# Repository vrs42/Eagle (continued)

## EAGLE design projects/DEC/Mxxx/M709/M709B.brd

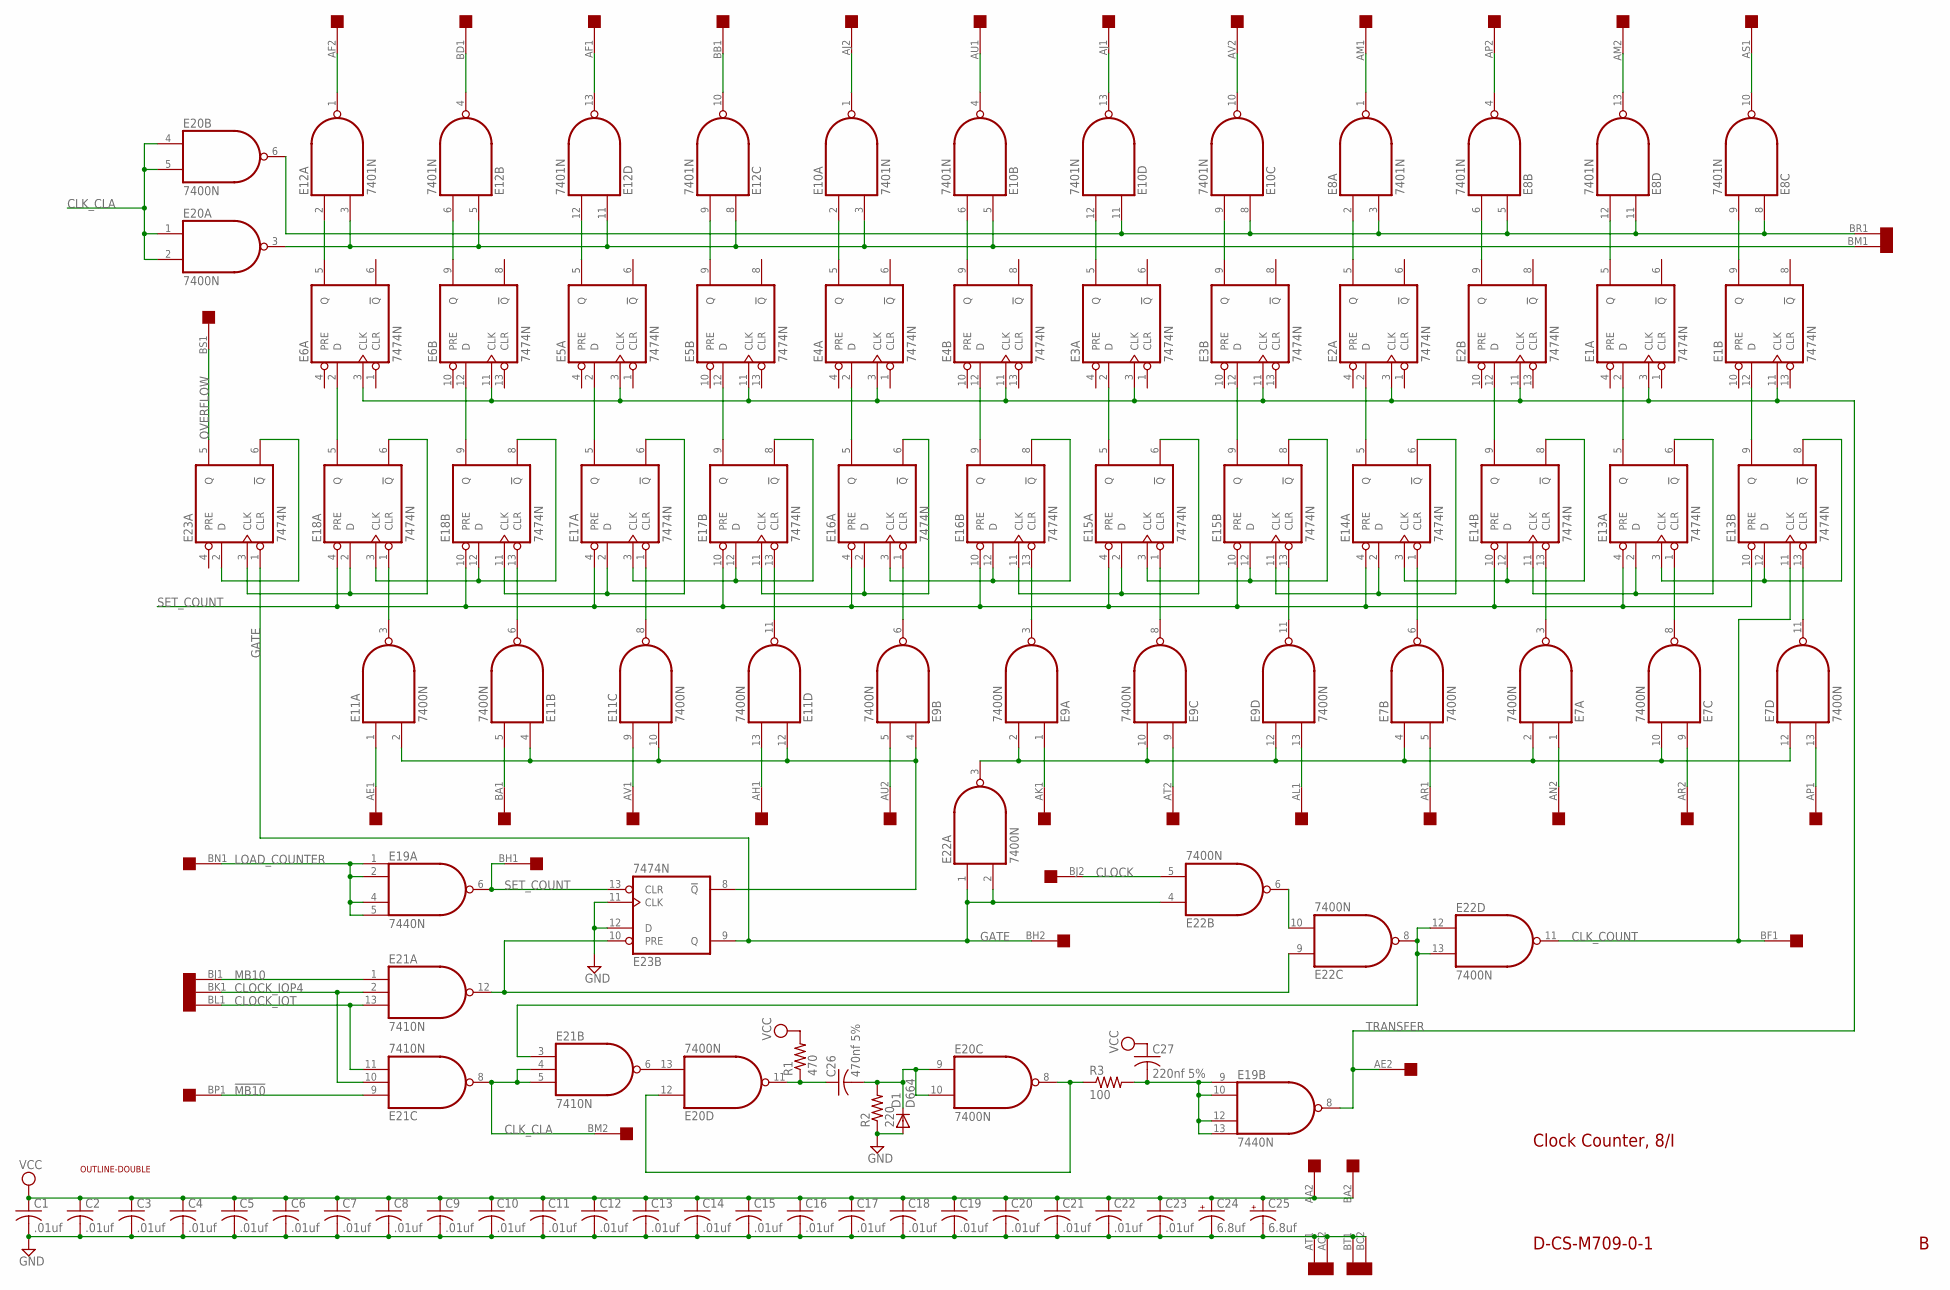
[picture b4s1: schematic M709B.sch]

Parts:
C1, C2, C3, C4, C5, C6, C7, C8, C9, C10, C11, C12, C13, C14, C15, C16, C17, C18, C19, C20, C21, C22, C23: .01uf; C050-025X075
C24, C25: 6.8uf; E15-5
C26: 470nf 5%; C050-025X075
C27: 220nf 5%; C050-025X075
D1: D664; DO35-10
E1, E2, E3, E4, E5, E6, E13, E14, E15, E16, E17, E18, E23: 7474N; DIL14
E7, E9, E11, E20, E22: 7400N; DIL14
E8, E10, E12: 7401N; DIL14
E19: 7440N; DIL14
E21: 7410N; DIL14
R1: 470; 0207/10
R2: 220; 0207/10
R3: 100; 0207/10
U$1: OUTLINE-DOUBLE; DOUBLE
U$2: DOUBLE; EDGE-CON4

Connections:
!MB10: E21.9 (I0), U$2.BP1
CLK_CLA: E20.1 (I0), E20.2 (I1), E20.4 (I0), E20.5 (I1), E21.4 (I1), E21.5 (I2), E21.8 (O), U$2.BM2
CLK_COUNT: E13.11 (CLK), E22.11 (O), U$2.BF1
CLOCK: E22.5 (I1), U$2.BJ2
CLOCK_IOP4: E21.2 (I1), E21.10 (I1), U$2.BK1
CLOCK_IOT: E21.11 (I2), E21.13 (I2), U$2.BL1
GATE: E22.1 (I0), E22.2 (I1), E22.4 (I0), E23.1 (CLR), E23.9 (Q), U$2.BH2
GND: C1.2, C2.2, C3.2, C4.2, C5.2, C6.2, C7.2, C8.2, C9.2, C10.2, C11.2, C12.2, C13.2, C14.2, C15.2, C16.2, C17.2, C18.2, C19.2, C20.2, C21.2, C22.2, C23.2, C24.-, C25.-, D1.A, E1.7 (GND), E2.7 (GND), E3.7 (GND), E4.7 (GND), E5.7 (GND), E6.7 (GND), E7.7 (GND), E8.7 (GND), E9.7 (GND), E10.7 (GND), E11.7 (GND), E12.7 (GND), E13.7 (GND), E14.7 (GND), E15.7 (GND), E16.7 (GND), E17.7 (GND), E18.7 (GND), E19.7 (GND), E20.7 (GND), E21.7 (GND), E22.7 (GND), E23.7 (GND), E23.11 (CLK), E23.12 (D), R2.1, U$2.AC2, U$2.AT1, U$2.BC2, U$2.BT1
LOAD_COUNTER: E19.1 (I0), E19.2 (I1), E19.4 (I2), E19.5 (I3), U$2.BN1
MB10: E21.1 (I0), U$2.BJ1
unnamed: E1.9 (Q), E8.9 (I1)
unnamed: E1.5 (Q), E8.12 (I1)
unnamed: E2.9 (Q), E8.6 (I1)
unnamed: E2.5 (Q), E8.2 (I0)
unnamed: E6.5 (Q), E12.2 (I0)
unnamed: E3.9 (Q), E10.9 (I1)
unnamed: E3.5 (Q), E10.12 (I1)
unnamed: E4.5 (Q), E10.2 (I0)
unnamed: E4.9 (Q), E10.6 (I1)
unnamed: E5.5 (Q), E12.12 (I1)
unnamed: E5.9 (Q), E12.9 (I1)
unnamed: E6.9 (Q), E12.6 (I1)
unnamed: E10.3 (I1), E10.5 (I0), E12.3 (I1), E12.5 (I0), E12.8 (I0), E12.11 (I0), E20.3 (O), U$2.BM1
unnamed: E8.1 (O), U$2.AM1
unnamed: E8.4 (O), U$2.AP2
unnamed: E8.13 (O), U$2.AM2
unnamed: E8.10 (O), U$2.AS1
unnamed: E10.13 (O), U$2.AJ1
unnamed: E10.4 (O), U$2.AU1
unnamed: E10.1 (O), U$2.AJ2
unnamed: E10.10 (O), U$2.AV2
unnamed: E12.1 (O), U$2.AF2
unnamed: E12.4 (O), U$2.BD1
unnamed: E12.13 (O), U$2.AF1
unnamed: E12.10 (O), U$2.BB1
unnamed: E8.3 (I1), E8.5 (I0), E8.8 (I0), E8.11 (I0), E10.8 (I0), E10.11 (I0), E20.6 (O), U$2.BR1
unnamed: E6.2 (D), E18.5 (Q)
unnamed: E6.12 (D), E18.9 (Q)
unnamed: E5.2 (D), E17.5 (Q)
unnamed: E5.12 (D), E17.9 (Q)
unnamed: E4.2 (D), E16.5 (Q)
unnamed: E4.12 (D), E16.9 (Q)
unnamed: E3.2 (D), E15.5 (Q)
unnamed: E3.12 (D), E15.9 (Q)
unnamed: E2.2 (D), E14.5 (Q)
unnamed: E2.12 (D), E14.9 (Q)
unnamed: E1.2 (D), E13.5 (Q)
unnamed: E1.12 (D), E13.9 (Q)
unnamed: E13.3 (CLK), E13.8 (!Q), E13.12 (D)
unnamed: E13.2 (D), E13.6 (!Q), E14.11 (CLK)
unnamed: E14.3 (CLK), E14.8 (!Q), E14.12 (D)
unnamed: E14.2 (D), E14.6 (!Q), E15.11 (CLK)
unnamed: E15.3 (CLK), E15.8 (!Q), E15.12 (D)
unnamed: E15.2 (D), E15.6 (!Q), E16.11 (CLK)
unnamed: E16.3 (CLK), E16.8 (!Q), E16.12 (D)
unnamed: E16.2 (D), E16.6 (!Q), E17.11 (CLK)
unnamed: E17.3 (CLK), E17.8 (!Q), E17.12 (D)
unnamed: E17.2 (D), E17.6 (!Q), E18.11 (CLK)
unnamed: E18.3 (CLK), E18.8 (!Q), E18.12 (D)
unnamed: E18.2 (D), E18.6 (!Q), E23.3 (CLK)
unnamed: E23.2 (D), E23.6 (!Q)
unnamed: E7.6 (O), E14.1 (CLR)
unnamed: E7.3 (O), E14.13 (CLR)
unnamed: E7.8 (O), E13.1 (CLR)
unnamed: E7.11 (O), E13.13 (CLR)
unnamed: E7.2 (I1), E7.4 (I0), E7.10 (I1), E7.12 (I0), E9.2 (I1), E9.10 (I1), E9.12 (I0), E22.3 (O)
unnamed: E9.4 (I0), E11.2 (I1), E11.4 (I0), E11.10 (I1), E11.12 (I0), E23.8 (!Q)
unnamed: E22.6 (O), E22.10 (I1)
unnamed: E7.13 (I1), U$2.AP1
unnamed: E9.6 (O), E16.1 (CLR)
unnamed: E9.3 (O), E16.13 (CLR)
unnamed: E9.8 (O), E15.1 (CLR)
unnamed: E9.11 (O), E15.13 (CLR)
unnamed: E11.11 (O), E17.13 (CLR)
unnamed: E11.8 (O), E17.1 (CLR)
unnamed: E11.6 (O), E18.13 (CLR)
unnamed: E11.3 (O), E18.1 (CLR)
unnamed: E7.9 (I0), U$2.AR2
unnamed: E7.1 (I0), U$2.AN2
unnamed: E7.5 (I1), U$2.AR1
unnamed: E9.13 (I1), U$2.AL1
unnamed: E9.1 (I0), U$2.AK1
unnamed: E9.9 (I0), U$2.AT2
unnamed: E11.9 (I0), U$2.AV1
unnamed: E11.13 (I1), U$2.AH1
unnamed: E9.5 (I1), U$2.AU2
unnamed: E11.1 (I0), U$2.AE1
unnamed: E11.5 (I1), U$2.BA1
unnamed: E21.12 (O), E22.9 (I0), E23.10 (PRE)
unnamed: E21.3 (I0), E22.8 (O), E22.12 (I0), E22.13 (I1)
unnamed: C26.2, D1.C, E20.9 (I0), E20.10 (I1), R2.2
unnamed: E20.13 (I1), E21.6 (O)
unnamed: C27.2, E19.9 (I0), E19.10 (I1), E19.12 (I2), E19.13 (I3), R3.2
unnamed: C26.1, E20.11 (O), R1.1
unnamed: E20.8 (O), E20.12 (I0), R3.1
OVERFLOW: E23.5 (Q), U$2.BS1
SET_COUNT: E13.4 (PRE), E13.10 (PRE), E14.4 (PRE), E14.10 (PRE), E15.4 (PRE), E15.10 (PRE), E16.4 (PRE), E16.10 (PRE), E17.4 (PRE), E17.10 (PRE), E18.4 (PRE), E18.10 (PRE), E19.6 (O), E23.13 (CLR), U$2.BH1
TRANSFER: E1.3 (CLK), E1.11 (CLK), E2.3 (CLK), E2.11 (CLK), E3.3 (CLK), E3.11 (CLK), E4.3 (CLK), E4.11 (CLK), E5.3 (CLK), E5.11 (CLK), E6.3 (CLK), E6.11 (CLK), E19.8 (O), U$2.AE2
VCC: C1.1, C2.1, C3.1, C4.1, C5.1, C6.1, C7.1, C8.1, C9.1, C10.1, C11.1, C12.1, C13.1, C14.1, C15.1, C16.1, C17.1, C18.1, C19.1, C20.1, C21.1, C22.1, C23.1, C24.+, C25.+, C27.1, E1.14 (VCC), E2.14 (VCC), E3.14 (VCC), E4.14 (VCC), E5.14 (VCC), E6.14 (VCC), E7.14 (VCC), E8.14 (VCC), E9.14 (VCC), E10.14 (VCC), E11.14 (VCC), E12.14 (VCC), E13.14 (VCC), E14.14 (VCC), E15.14 (VCC), E16.14 (VCC), E17.14 (VCC), E18.14 (VCC), E19.14 (VCC), E20.14 (VCC), E21.14 (VCC), E22.14 (VCC), E23.14 (VCC), R1.2, U$2.AA2, U$2.BA2

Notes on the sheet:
Clock Counter, 8/I
D-CS-M709-0-1

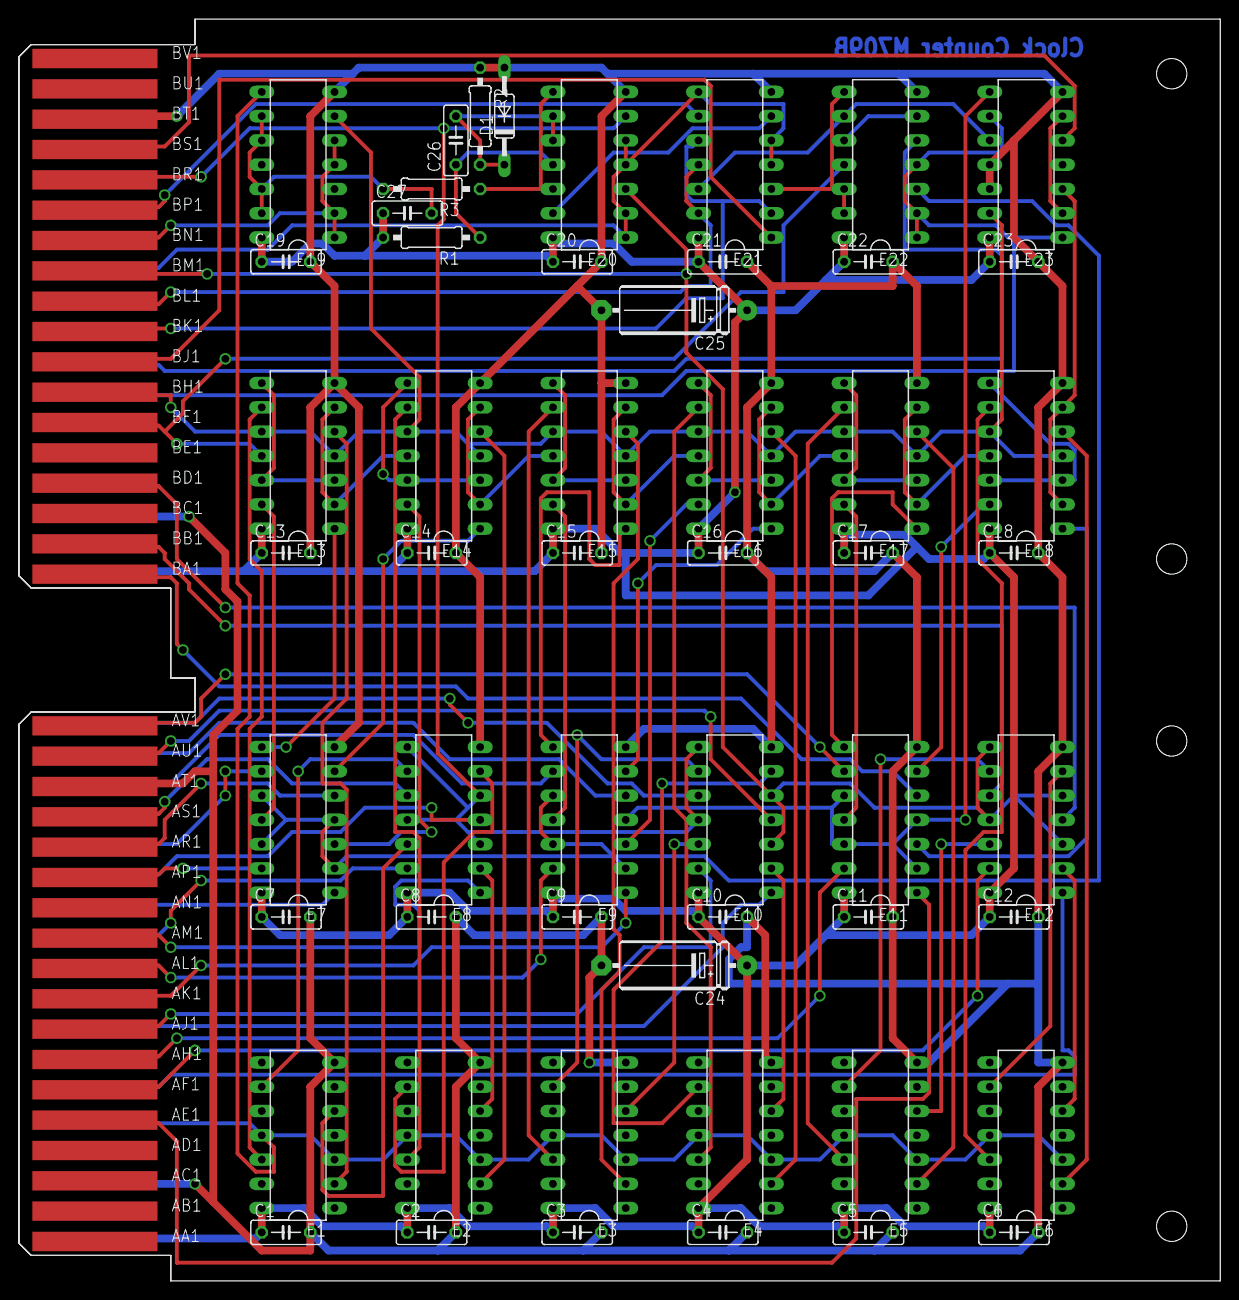
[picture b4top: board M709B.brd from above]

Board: 2 copper layers, 125.7 x 132.1 mm, 56 parts (0 on the bottom side), 99 nets.

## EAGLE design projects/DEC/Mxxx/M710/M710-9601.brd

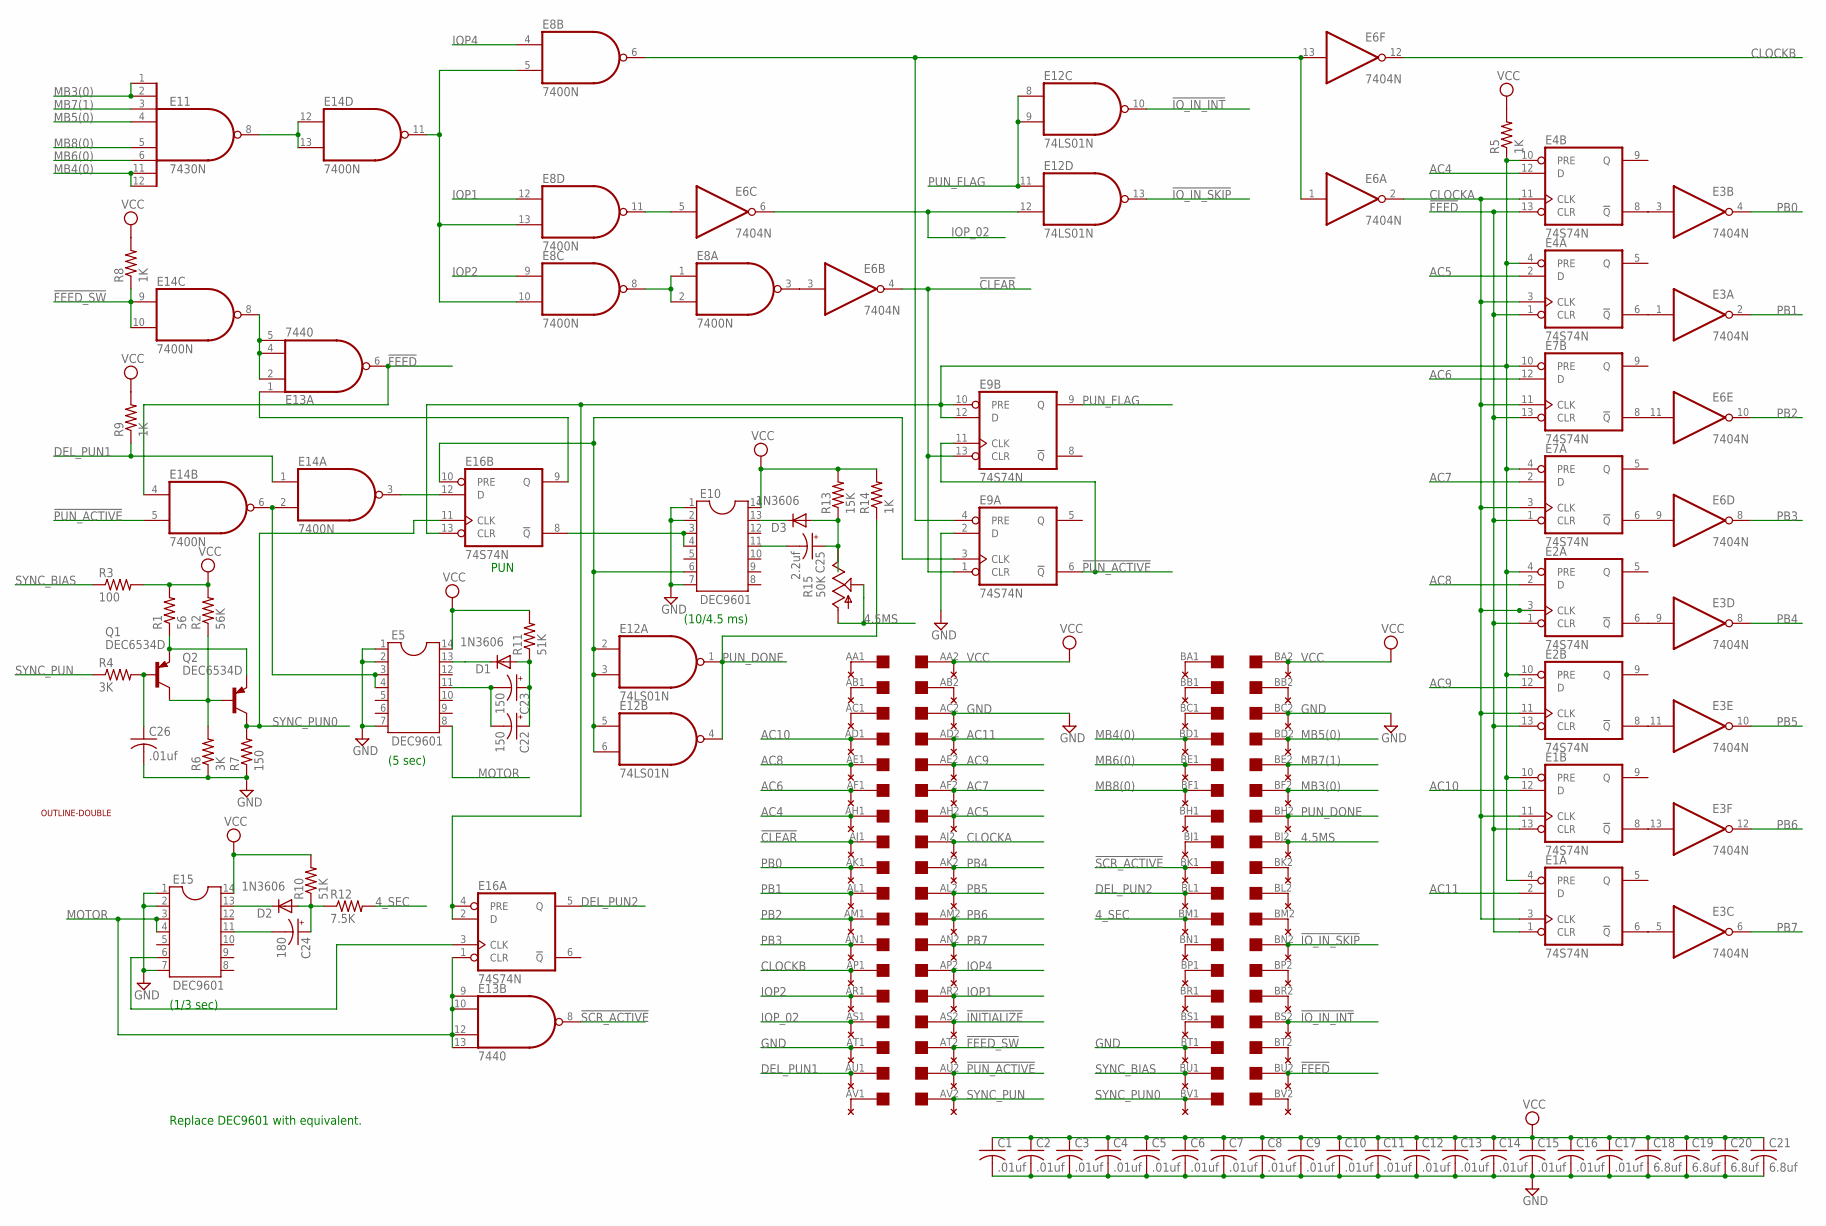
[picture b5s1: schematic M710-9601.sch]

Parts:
C1, C2, C3, C4, C5, C6, C7, C8, C9, C10, C11, C12, C13, C14, C15, C16, C17, C26: .01uf; C050-025X075
C18, C19, C20, C21: 6.8uf; C150-054X183
C22, C23: 150; E5-8,5
C24: 180; E5-8,5
C25: 2.2uf; E5-8,5
D1, D2, D3: 1N3606; DO41-10
E1, E2, E4, E7, E9, E16: 74S74N; DIL14
E3, E6: 7404N; DIL14
E5, E10, E15: DEC9601; DIL14
E8, E14: 7400N; DIL14
E11: 7430N; DIL14
E12: 74LS01N; DIL14
E13: 7440; DIL14
Q1, Q2: DEC6534D; TO92
R1: 56; 0207/7
R2: 56K; 0207/7
R3: 100; 0207/7
R4, R6: 3K; 0207/7
R5, R8, R9, R14: 1K; 0207/7
R7: 150; 0207/7
R10, R11: 51K; 0207/7
R12: 7.5K; 0207/7
R13: 15K; 0207/7
R15: 50K; PT-SPIN
U$1: OUTLINE-DOUBLE; DOUBLE
U$2: DOUBLE; EDGE-CON4
U$5, U$7: THRU-HOLE2B; THRU-HOLEB

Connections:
4.5MS: R15.A, R15.S, U$2.BJ2, U$5.J2
4_SEC: R12.2, U$2.BM1, U$5.M1
!CLEAR: E6.4 (O), E9.1 (CLR), E9.13 (CLR), U$2.AJ1, U$7.J1
!FEED: E1.1 (CLR), E1.13 (CLR), E2.1 (CLR), E2.13 (CLR), E4.1 (CLR), E4.13 (CLR), E7.1 (CLR), E7.13 (CLR), E13.6 (O), E14.4 (I0), U$2.BU2, U$5.U2
!FEED_SW: E14.9 (I0), E14.10 (I1), R8.1, U$2.AT2, U$7.T2
!INITIALIZE: U$2.AS2, U$7.S2
!IO_IN_INT: E12.10 (O), U$2.BS2, U$5.S2
!IO_IN_SKIP: E12.13 (O), U$2.BN2, U$5.N2
!PUN_ACTIVE: E9.6 (!Q), E9.11 (CLK), E14.5 (I1), U$2.AU2, U$7.U2
!SCR_ACTIVE: E13.8 (O), U$2.BK1, U$5.K1
AC4: E4.12 (D), U$2.AH1, U$7.H1
AC5: E4.2 (D), U$2.AH2, U$7.H2
AC6: E7.12 (D), U$2.AF1, U$7.F1
AC7: E7.2 (D), U$2.AF2, U$7.F2
AC8: E2.2 (D), U$2.AE1, U$7.E1
AC9: E2.12 (D), U$2.AE2, U$7.E2
AC10: E1.12 (D), U$2.AD1, U$7.D1
AC11: E1.2 (D), U$2.AD2, U$7.D2
CLOCKA: E1.3 (CLK), E1.11 (CLK), E2.3 (CLK), E2.11 (CLK), E4.3 (CLK), E4.11 (CLK), E6.2 (O), E7.3 (CLK), E7.11 (CLK), U$2.AJ2, U$7.J2
CLOCKB: E6.12 (O), U$2.AP1, U$7.P1
DEL_PUN1: E14.1 (I0), R9.1, U$2.AU1, U$7.U1
DEL_PUN2: E16.5 (Q), U$2.BL1, U$5.L1
GND: C1.2, C2.2, C3.2, C4.2, C5.2, C6.2, C7.2, C8.2, C9.2, C10.2, C11.2, C12.2, C13.2, C14.2, C15.2, C16.2, C17.2, C18.2, C19.2, C20.2, C21.2, C26.2, E1.7 (GND), E2.7 (GND), E3.7 (GND), E4.7 (GND), E5.1, E5.2, E5.7, E6.7 (GND), E7.7 (GND), E8.7 (GND), E9.2 (D), E9.7 (GND), E10.1, E10.2, E10.7, E11.7 (GND), E12.7 (GND), E13.7 (GND), E14.7 (GND), E15.1, E15.2, E15.7, E16.7 (GND), R6.1, R7.1, U$2.AC2, U$2.AT1, U$2.BC2, U$2.BT1, U$5.C2, U$5.T1, U$7.C2, U$7.T1
IOP1: E8.12 (I0), U$2.AR2, U$7.R2
IOP2: E8.9 (I0), U$2.AR1, U$7.R1
IOP4: E8.4 (I0), U$2.AP2, U$7.P2
IOP_02: E6.6 (O), E12.12 (I1), U$2.AS1, U$7.S1
MB3(0): E11.1 (I0), E11.2 (I1), U$2.BF2, U$5.F2
MB4(0): E11.11 (I6), E11.12 (I7), U$2.BD1, U$5.D1
MB5(0): E11.4 (I3), U$2.BD2, U$5.D2
MB6(0): E11.6 (I5), U$2.BE1, U$5.E1
MB7(1): E11.3 (I2), U$2.BE2, U$5.E2
MB8(0): E11.5 (I4), U$2.BF1, U$5.F1
MOTOR: E5.8, E13.9 (I0), E13.10 (I1), E13.12 (I2), E13.13 (I3), E15.3, E15.4, E16.1 (CLR)
unnamed: U$2.AB2, U$7.B2
unnamed: E3.3 (I), E4.8 (!Q)
unnamed: E3.1 (I), E4.6 (!Q)
unnamed: E6.1 (I), E6.13 (I), E8.6 (O), E9.4 (PRE)
unnamed: E11.8 (O), E14.12 (I0), E14.13 (I1)
unnamed: E6.3 (I), E8.3 (O)
unnamed: E8.1 (I0), E8.2 (I1), E8.8 (O)
unnamed: E8.5 (I1), E8.10 (I1), E8.13 (I1), E14.11 (O)
unnamed: E2.6 (!Q), E3.9 (I)
unnamed: E2.8 (!Q), E3.11 (I)
unnamed: E1.8 (!Q), E3.13 (I)
unnamed: E1.6 (!Q), E3.5 (I)
unnamed: E6.11 (I), E7.8 (!Q)
unnamed: E6.9 (I), E7.6 (!Q)
unnamed: U$2.AV1, U$7.V1
unnamed: E6.5 (I), E8.11 (O)
unnamed: U$2.AC1, U$7.C1
unnamed: U$2.AB1, U$7.B1
unnamed: Q1.1 (C), Q2.2 (B), R2.1, R6.2
unnamed: U$2.BS1, U$5.S1
unnamed: U$2.BR1, U$5.R1
unnamed: U$2.BP1, U$5.P1
unnamed: U$2.BN1, U$5.N1
unnamed: U$2.AA1, U$7.A1
unnamed: U$2.BJ1, U$5.J1
unnamed: U$2.BH1, U$5.H1
unnamed: U$2.BC1, U$5.C1
unnamed: U$2.BB1, U$5.B1
unnamed: U$2.BA1, U$5.A1
unnamed: U$2.BV2, U$5.V2
unnamed: U$2.BT2, U$5.T2
unnamed: U$2.BR2, U$5.R2
unnamed: U$2.BP2, U$5.P2
unnamed: Q1.3 (E), Q2.3 (E), R1.1
unnamed: U$2.BM2, U$5.M2
unnamed: C26.1, Q1.2 (B), R4.2
unnamed: U$2.BL2, U$5.L2
unnamed: C24.-, E15.11
unnamed: E13.2 (I1), E13.4 (I2), E13.5 (I3), E14.8 (O)
unnamed: U$2.BK2, U$5.K2
unnamed: U$2.BB2, U$5.B2
unnamed: E1.4 (PRE), E1.10 (PRE), E2.4 (PRE), E2.10 (PRE), E4.4 (PRE), E4.10 (PRE), E7.4 (PRE), E7.10 (PRE), E9.10 (PRE), E9.12 (D), E16.2 (D), E16.4 (PRE), E16.13 (CLR), R5.1
unnamed: C25.-, E10.11
unnamed: E13.1 (I0), E16.9 (Q)
unnamed: E14.3 (O), E16.12 (D)
unnamed: E5.3, E5.4, E14.2 (I1), E14.6 (O)
unnamed: C22.-, C23.-, E5.11
unnamed: D1.C, E5.13
unnamed: C22.+, C23.+, D1.A, R11.1
unnamed: D2.C, E15.13
unnamed: C24.+, D2.A, R10.1, R12.1
unnamed: E15.6, E16.3 (CLK)
unnamed: D3.C, E10.13
unnamed: C25.+, D3.A, R13.1, R15.E
unnamed: E10.3, E10.4, E16.8 (!Q)
unnamed: E9.3 (CLK), E10.6, E12.2 (I0), E12.3 (I1), E12.5 (I0), E12.6 (I1), E16.10 (PRE)
PB0: E3.4 (O), U$2.AK1, U$7.K1
PB1: E3.2 (O), U$2.AL1, U$7.L1
PB2: E6.10 (O), U$2.AM1, U$7.M1
PB3: E6.8 (O), U$2.AN1, U$7.N1
PB4: E3.8 (O), U$2.AK2, U$7.K2
PB5: E3.10 (O), U$2.AL2, U$7.L2
PB6: E3.12 (O), U$2.AM2, U$7.M2
PB7: E3.6 (O), U$2.AN2, U$7.N2
PUN_DONE: E12.1 (O), E12.4 (O), R14.1, U$2.BH2, U$5.H2
PUN_FLAG: E9.9 (Q), E12.8 (I0), E12.9 (I1), E12.11 (I0)
SYNC_BIAS: R3.1, U$2.BU1, U$5.U1
SYNC_PUN: R4.1, U$2.AV2, U$7.V2
SYNC_PUN0: E16.11 (CLK), Q2.1 (C), R7.2, U$2.BV1, U$5.V1
VCC: C1.1, C2.1, C3.1, C4.1, C5.1, C6.1, C7.1, C8.1, C9.1, C10.1, C11.1, C12.1, C13.1, C14.1, C15.1, C16.1, C17.1, C18.1, C19.1, C20.1, C21.1, E1.14 (VCC), E2.14 (VCC), E3.14 (VCC), E4.14 (VCC), E5.14, E6.14 (VCC), E7.14 (VCC), E8.14 (VCC), E9.14 (VCC), E10.14, E11.14 (VCC), E12.14 (VCC), E13.14 (VCC), E14.14 (VCC), E15.14, E16.14 (VCC), R1.2, R2.2, R3.2, R5.2, R8.2, R9.2, R10.2, R11.2, R13.2, R14.2, U$2.AA2, U$2.BA2, U$5.A2, U$7.A2

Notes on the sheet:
(5 sec)
(1/3 sec)
(10/4.5 ms)
PUN
Replace DEC9601 with equivalent.

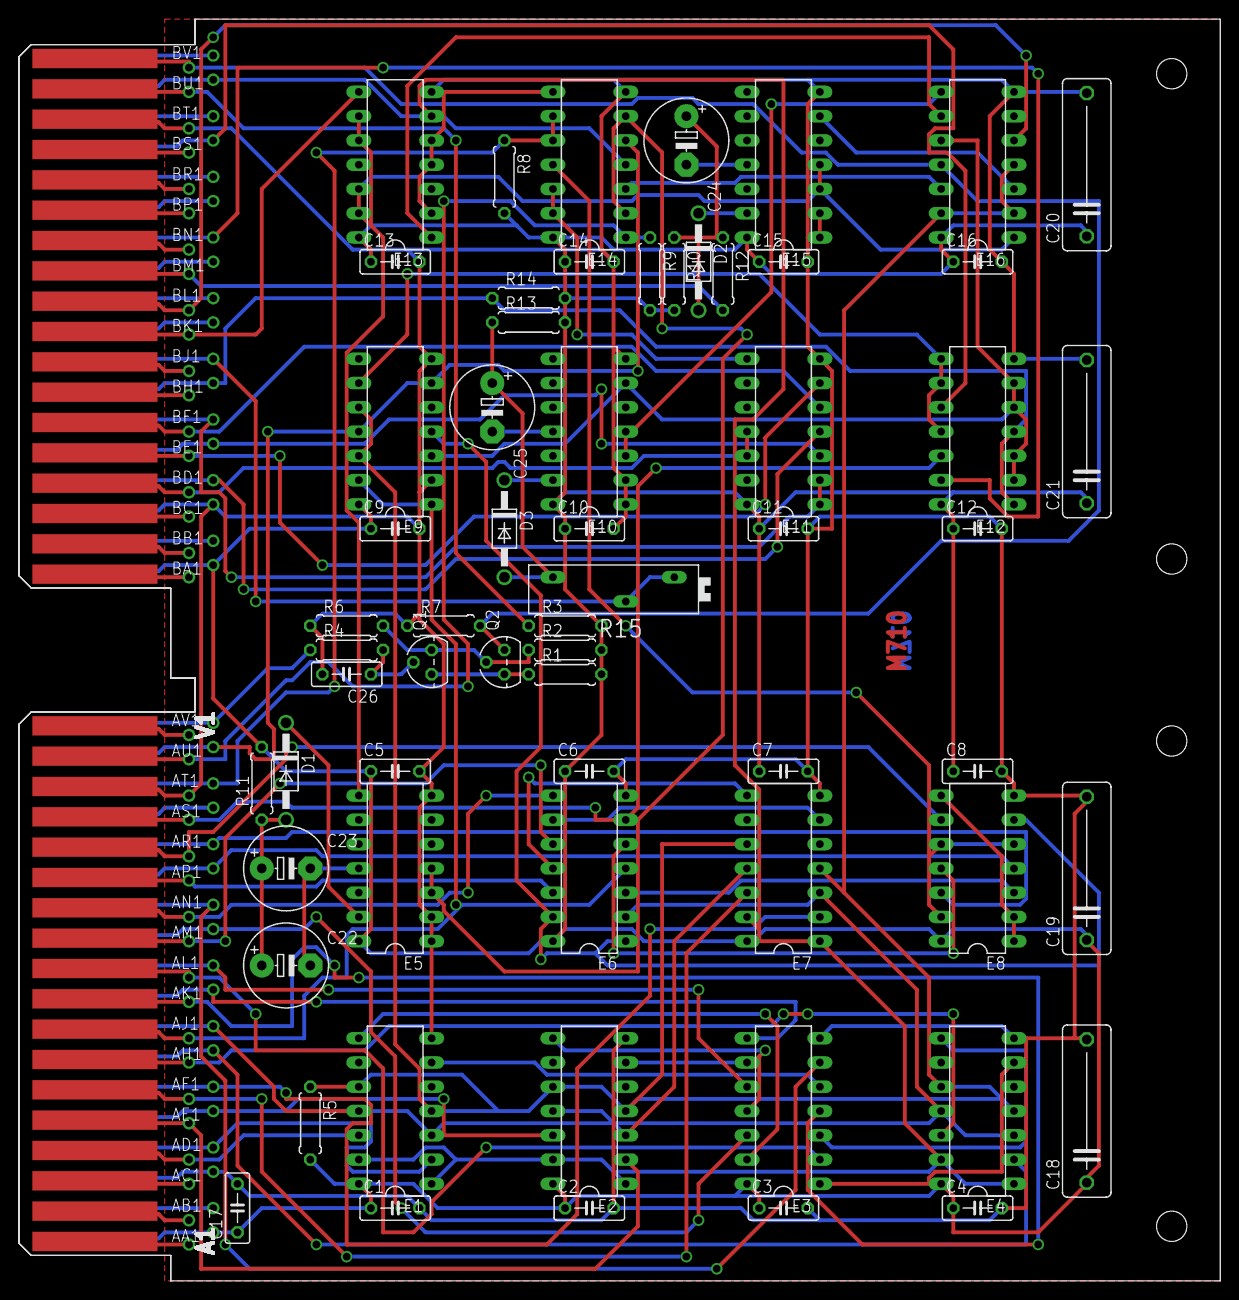
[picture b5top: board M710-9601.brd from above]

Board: 2 copper layers, 125.7 x 132.1 mm, 66 parts (0 on the bottom side), 104 nets.
